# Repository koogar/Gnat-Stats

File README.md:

Gnat-Stats is an open-source project that transforms a small OLED display into a real-time PC hardware performance monitor using Arduino-compatible microcontrollers. It visually presents metrics like CPU and GPU temperatures, loads, and system memory usage.([GitHub][1], [GitHub][2])

---

## 🔧 Features

* **Real-Time Monitoring**: Displays CPU/GPU temperatures, loads, and system RAM usage.
* **Compact Design**: Utilizes SSD1306 or SH1106 OLED displays for a minimal footprint.
* **Customizable Layouts**: Offers multiple display styles and anti-burn features.
* **Hardware Compatibility**: Supports boards like Seeeduino XIAO, Adafruit QT Py, and ESP32.
* **Serial Communication**: Receives data from a Windows client via USB serial.([GitHub][3])

---

## 🛠️ Getting Started

1. **Hardware Setup**:

   * Connect an SSD1306 or SH1106 OLED display to your microcontroller.
   * Ensure proper I2C connections and address configuration.([GitHub][3])
   * For detailed setup guides and tutorials, refer to the [Gnat-Stats OLED Display Hook-Up Guide](https://runawaybrainz.blogspot.com/2021/03/phat-stats-ssd1306-oled-hook-up-guide.html).

2. **Software Installation**:

   * Install necessary Arduino libraries:

     * Adafruit NeoPixel
     * Adafruit SSD1306
     * Adafruit SH110X
     * Adafruit GFX
     * Adafruit BusIO
   * Configure your board using the appropriate Board Manager URLs:

     * For Seeeduino XIAO:

       ```
       https://files.seeedstudio.com/arduino/package_seeeduino_boards_index.json
       ```

3. **Firmware Upload**:

   * Open the desired `.ino` file (e.g., `GnatStats_V1.7.Base.ino`) in the Arduino IDE.
   * Select the correct board and port.
   * Upload the sketch to your microcontroller.([GitHub][3])

4. **Windows Client**:

   * Install the [HardwareSerialMonitor](https://github.com/koogar/HardwareSerialMonitor) on your Windows PC to relay performance data.
3. **Configuration**:

   * Adjust settings within the Gnat-Stats firmware and HardwareSerialMonitor to match your hardware setup and monitoring preferences.

---

## 📜 License

This project is licensed under the [GPL-2.0 License](https://github.com/koogar/Gnat-Stats/blob/master/LICENSE.txt).

Gnat-Stats, Phat-Stats, Tacho-Stats, uVolume & HardwareSerialMonitor 
Copyright (C) 2016  Colin Conway, Rupert Hirst and contributors
 
This program is free software; you can redistribute it and/or
modify it under the terms of the GNU General Public License
as published by the Free Software Foundation; either version 2
of the License, or (at your option) any later version.

This program is distributed in the hope that it will be useful,
but WITHOUT ANY WARRANTY; without even the implied warranty of
MERCHANTABILITY or FITNESS FOR A PARTICULAR PURPOSE.  See the
GNU General Public License for more details.

You should have received a copy of the GNU General Public License
along with this program; If not, see <http://www.gnu.org/licenses/>.

---

For more details, visit the [Gnat-Stats GitHub Repository](https://github.com/koogar/Gnat-Stats).

[1]: https://github.com/koogar/Gnat-Stats/releases?utm_source=chatgpt.com "Releases · koogar/Gnat-Stats - GitHub"
[2]: https://github.com/koogar/Gnat-Stats/blob/master/GnatStats_V1.7.Base/DisplayStats.ino?utm_source=chatgpt.com "Gnat-Stats/GnatStats_V1.7.Base/DisplayStats.ino at master - GitHub"
[3]: https://github.com/koogar/Gnat-Stats/blob/master/GnatStats_V1.7.Base/GnatStats_V1.7.Base.ino?utm_source=chatgpt.com "Gnat-Stats/GnatStats_V1.7.Base/GnatStats_V1.7.Base.ino at ... - GitHub"
[4]: https://github.com/koogar/Gnat-Stats?utm_source=chatgpt.com "GitHub - koogar/Gnat-Stats: GnatStats Tiny OLED Arduino PC Hardware ..."

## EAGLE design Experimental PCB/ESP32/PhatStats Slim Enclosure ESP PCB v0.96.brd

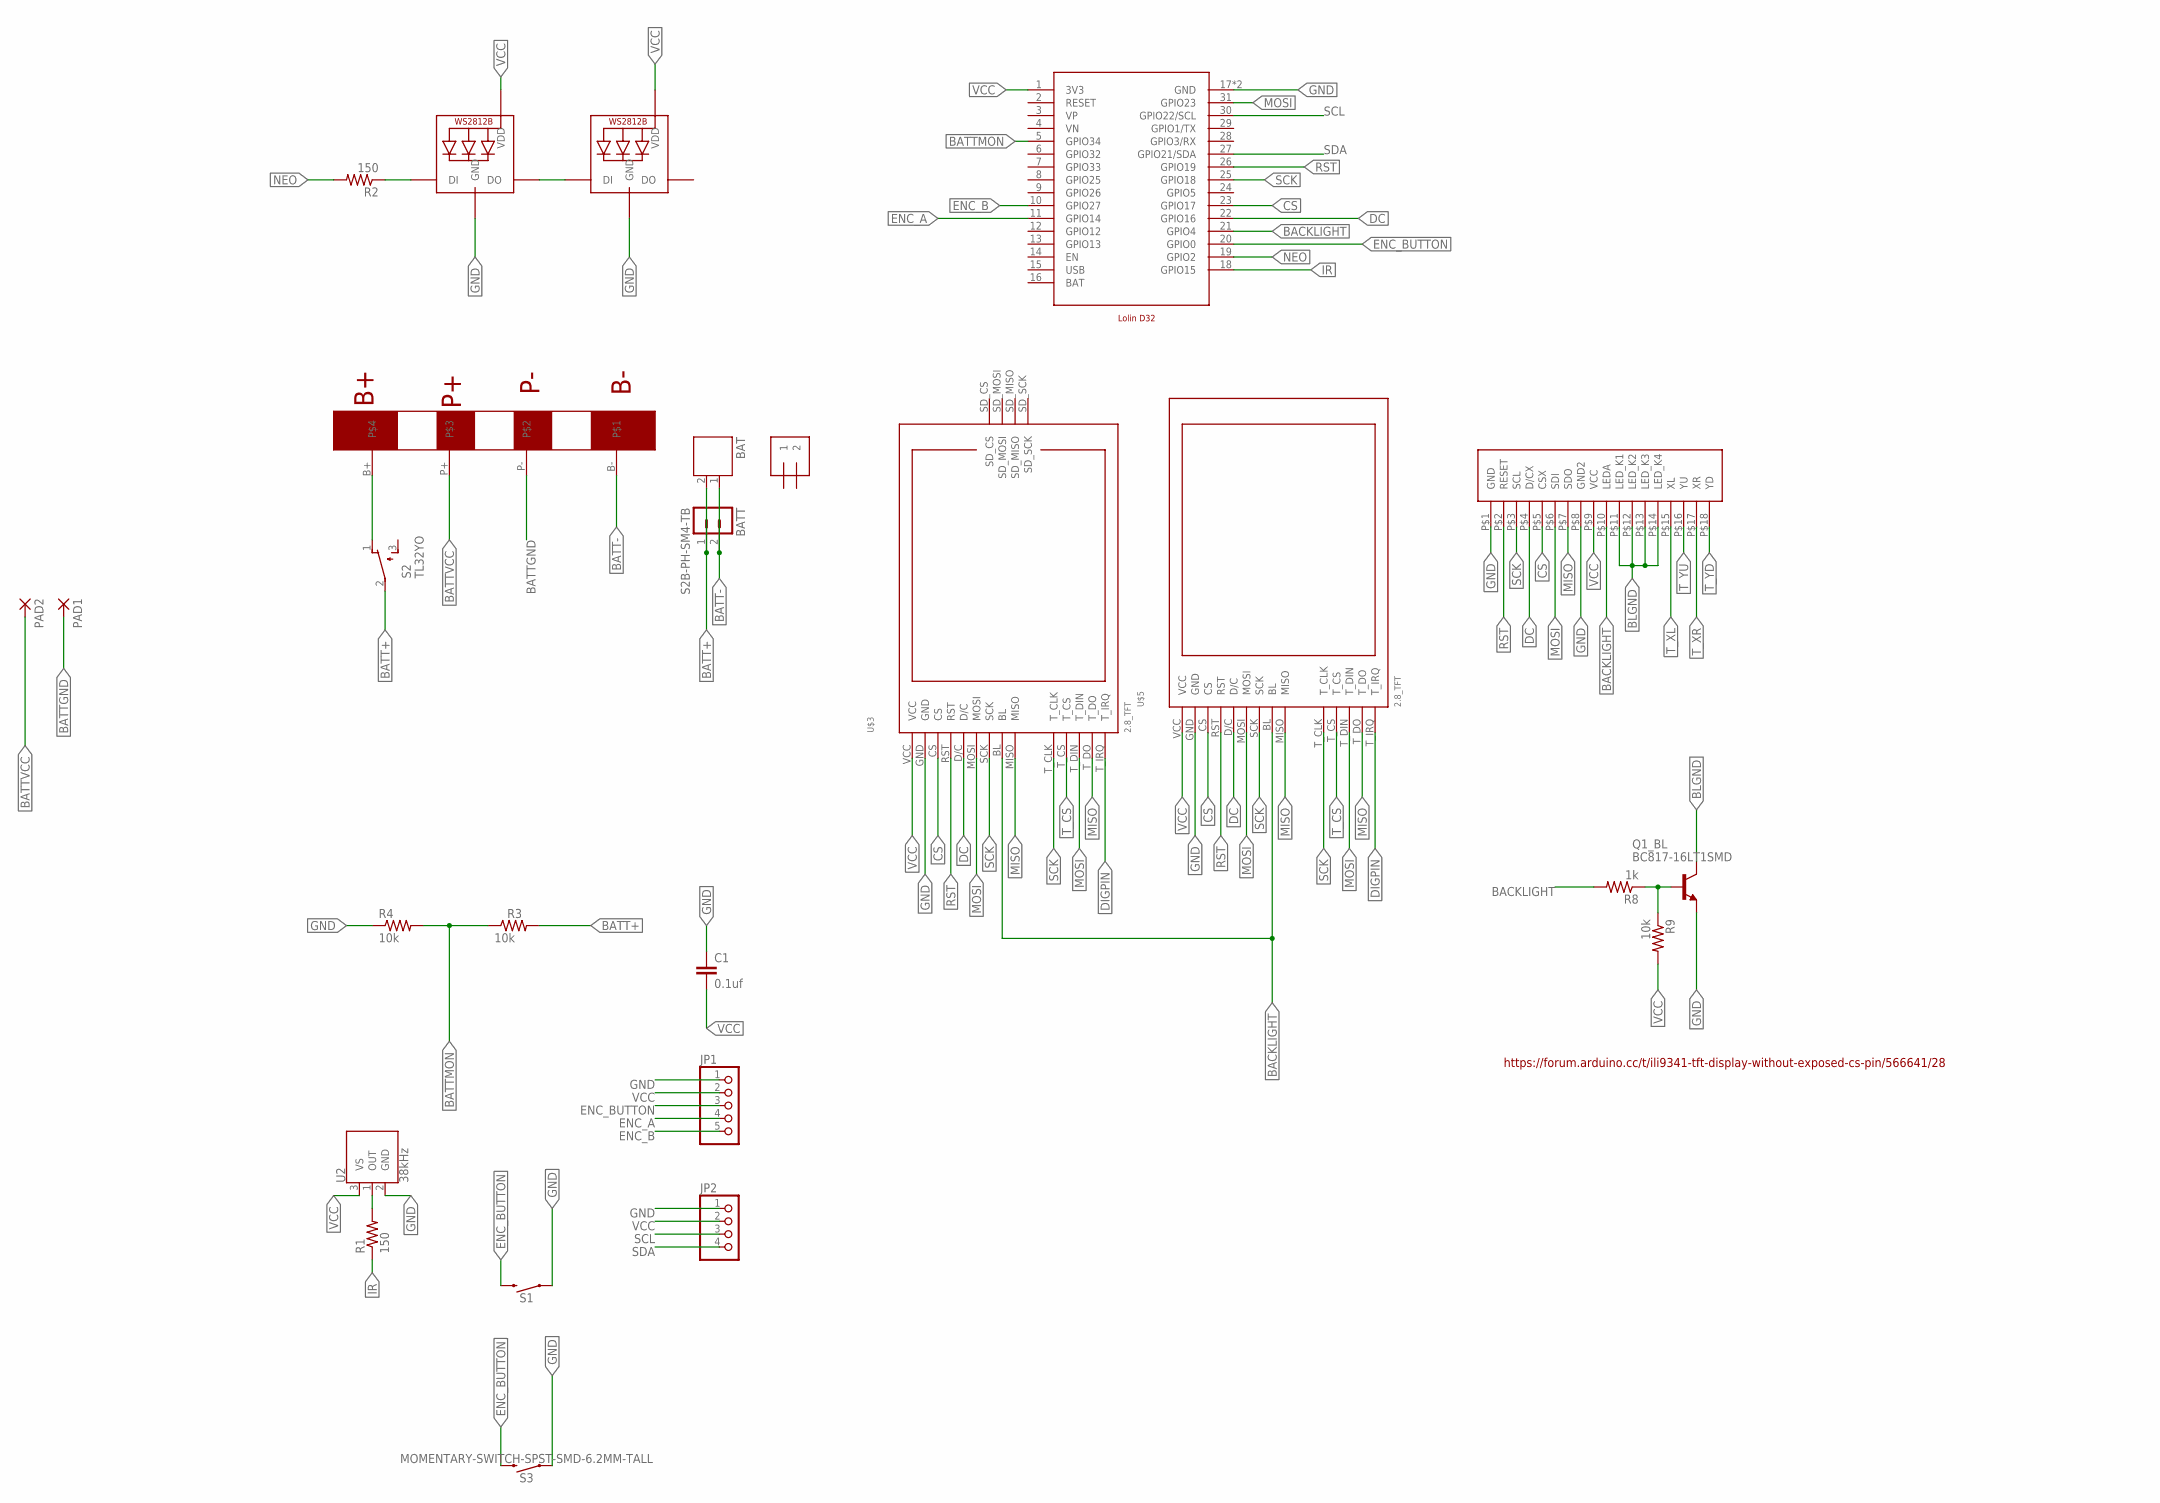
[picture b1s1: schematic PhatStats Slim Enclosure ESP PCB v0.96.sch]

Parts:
0: ILI9341-2.8
BAT: JST-PH2
BATT: S2B-PH-SM4-TB
BMS: DW01BATTERYPROT
C1: 0.1uf; C1206
J1: 1X2-3.5MM
JP1: PINHD-1X5; 1X05
JP2: PINHD-1X4; 1X04
NEO1, NEO2: WS2812B5050; WS2812B
PAD1, PAD2: WIREPADSMD5-1,8; 5-1,8
Q1_BL: BC817-16LT1SMD; SOT23-BEC
R1, R2: 150; M1206
R3, R4, R9: 10k; M1206
R8: 1k; M1206
S1: MOMENTARY-SWITCH-SPST-PTH-6.0MM; TACTILE_SWITCH_PTH_6.0MM
S2: TL32YO; TL3XYO
S3: MOMENTARY-SWITCH-SPST-SMD-6.2MM-TALL; TACTILE_SWITCH_SMD_6.2MM_TALL
U2: 38kHz; TSOP382
U$2: LOLIND32
U$3, U$5: 2.8_TFT

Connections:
BACKLIGHT: 0.P$10 (LEDA), R8.2, U$2.21 (GPIO4), U$3.BL, U$5.BL
BAT: U$2.16 (BAT)
BATT+: BAT.2, BATT.1, R3.2, S2.2
BATT-: BAT.1, BATT.2, BMS.B-
BATTGND: BMS.P-, PAD1.1
BATTMON: R3.1, R4.2, U$2.5 (GPIO34)
BATTVCC: BMS.P+, PAD2.1
BLGND: 0.P$11 (LED_K1), 0.P$12 (LED_K2), 0.P$13 (LED_K3), 0.P$14 (LED_K4), Q1_BL.C
CS: 0.P$5 (CSX), U$2.23 (GPIO17), U$3.CS, U$5.CS
DC: 0.P$4 (D/CX), U$2.22 (GPIO16), U$3.D/C, U$5.D/C
DIGPIN: U$3.T_IRQ, U$5.T_IRQ
ENC_A: JP1.4, U$2.11 (GPIO14)
ENC_B: JP1.5, U$2.10 (GPIO27)
ENC_BUTTON: JP1.3, S1.3 (2), S3.B2 (2), U$2.20 (GPIO0)
GND: 0.P$1 (GND), 0.P$8 (GND2), C1.1, JP1.1, JP2.1, NEO1.3-GND (GND), NEO2.3-GND (GND), Q1_BL.E, R4.1, S1.1, S3.A2 (1), U2.2 (GND), U$2.17 (GND), U$2.32 (GND), U$3.GND, U$5.GND
IR: R1.1, U$2.18 (GPIO15)
MISO: 0.P$7 (SDO), U$3.MISO, U$3.T_DO, U$5.MISO, U$5.T_DO
MOSI: 0.P$6 (SDI), U$2.31 (GPIO23), U$3.MOSI, U$3.T_DIN, U$5.MOSI, U$5.T_DIN
unnamed: BMS.B+, S2.1 (O)
unnamed: NEO1.2-DOUT (DO), NEO2.4-DIN (DI)
unnamed: R1.2, U2.1 (OUT)
unnamed: NEO1.4-DIN (DI), R2.1
unnamed: Q1_BL.B, R8.1, R9.1
NEO: R2.2, U$2.19 (GPIO2)
RST: 0.P$2 (RESET), U$2.26 (GPIO19), U$3.RST, U$5.RST
SCK: 0.P$3 (SCL), U$2.25 (GPIO18), U$3.SCK, U$3.T_CLK, U$5.SCK, U$5.T_CLK
SCL: JP2.3, U$2.30 (GPIO22/SCL)
SDA: JP2.4, U$2.27 (GPIO21/SDA)
T_CS: U$3.T_CS, U$5.T_CS
T_XL: 0.P$15 (XL)
T_XR: 0.P$17 (XR)
T_YD: 0.P$18 (YD)
T_YU: 0.P$16 (YU)
USB: U$2.15 (USB)
VCC: 0.P$9 (VCC), C1.2, JP1.2, JP2.2, NEO1.1-VDD (VDD), NEO2.1-VDD (VDD), R9.2, U2.3 (VS), U$2.1 (3V3), U$3.VCC, U$5.VCC

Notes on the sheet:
https://forum.arduino.cc/t/ili9341-tft-display-without-exposed-cs-pin/566641/28

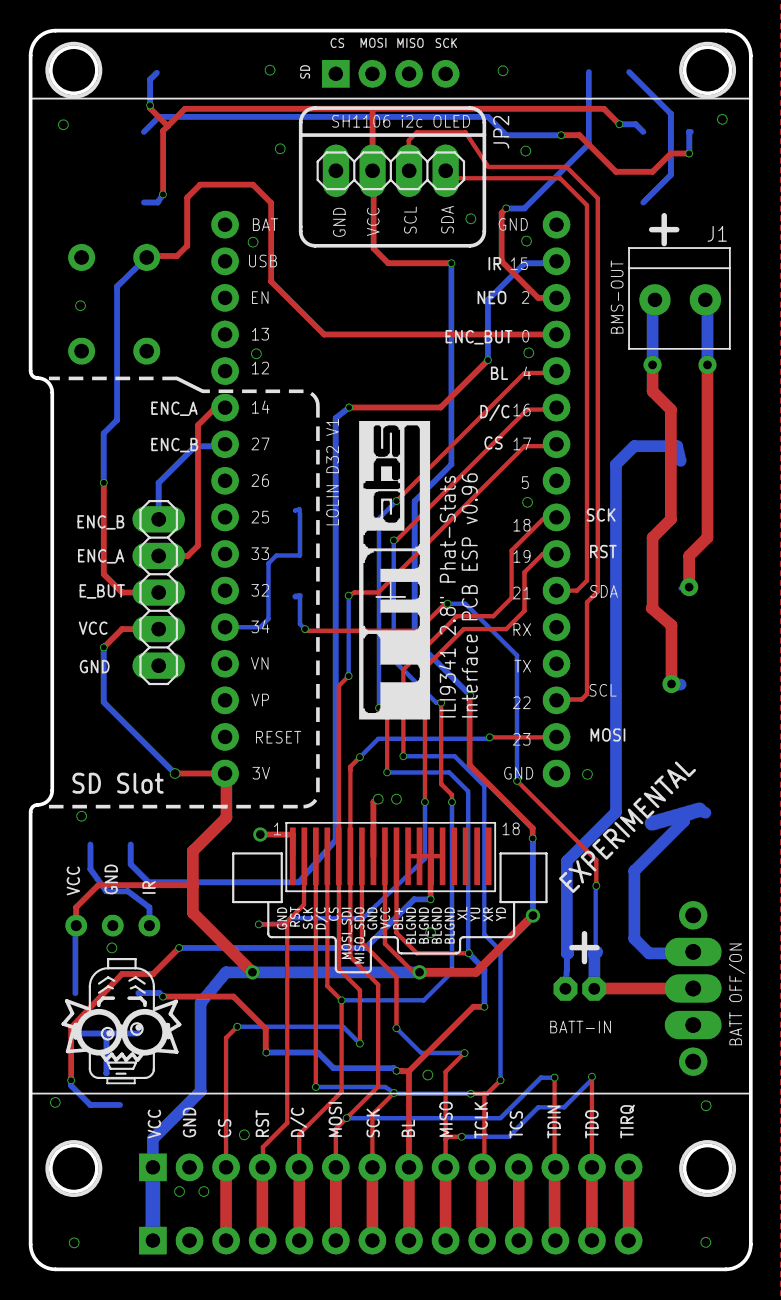
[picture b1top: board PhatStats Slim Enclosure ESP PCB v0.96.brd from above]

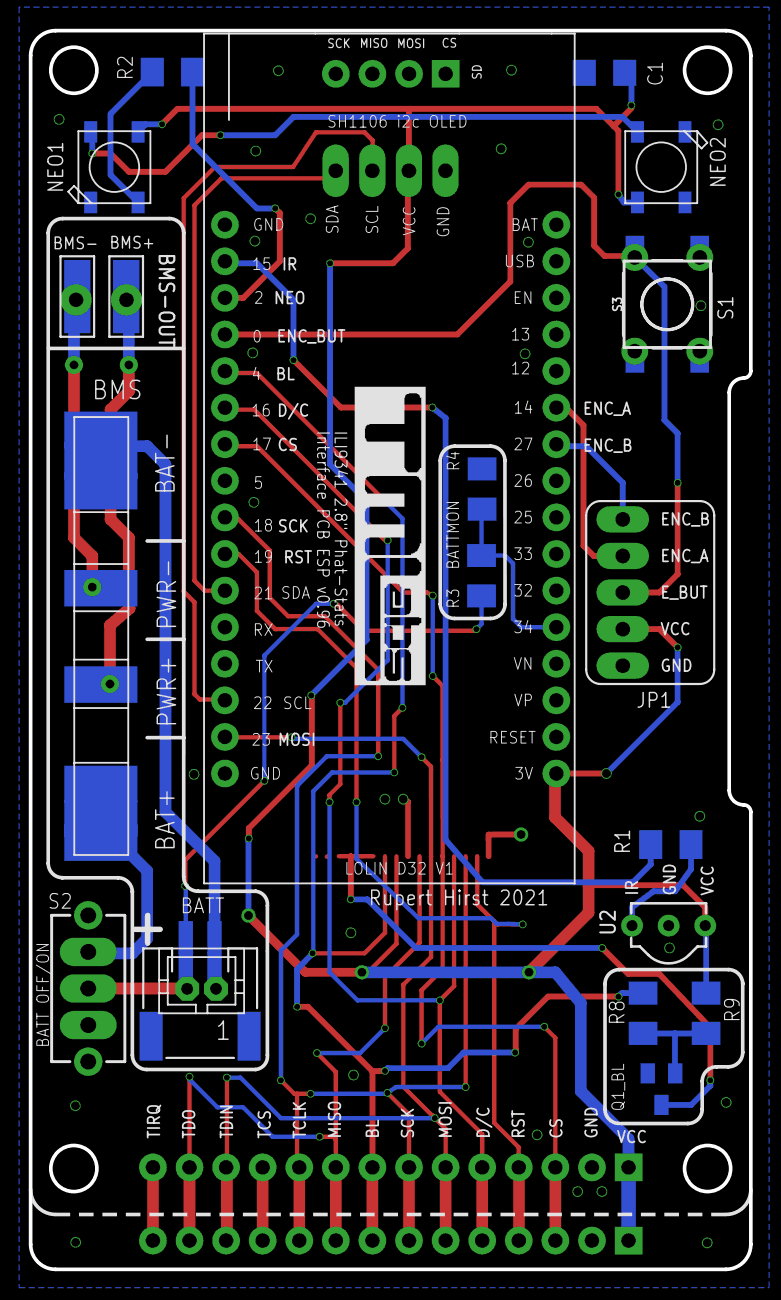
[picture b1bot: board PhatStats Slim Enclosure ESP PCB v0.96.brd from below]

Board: 2 copper layers, 50.0 x 86.0 mm, 29 parts (21 on the bottom side), 29 nets.

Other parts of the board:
U$6: MADPROF
U$9, U$10: TMSLOGO_INVERTED

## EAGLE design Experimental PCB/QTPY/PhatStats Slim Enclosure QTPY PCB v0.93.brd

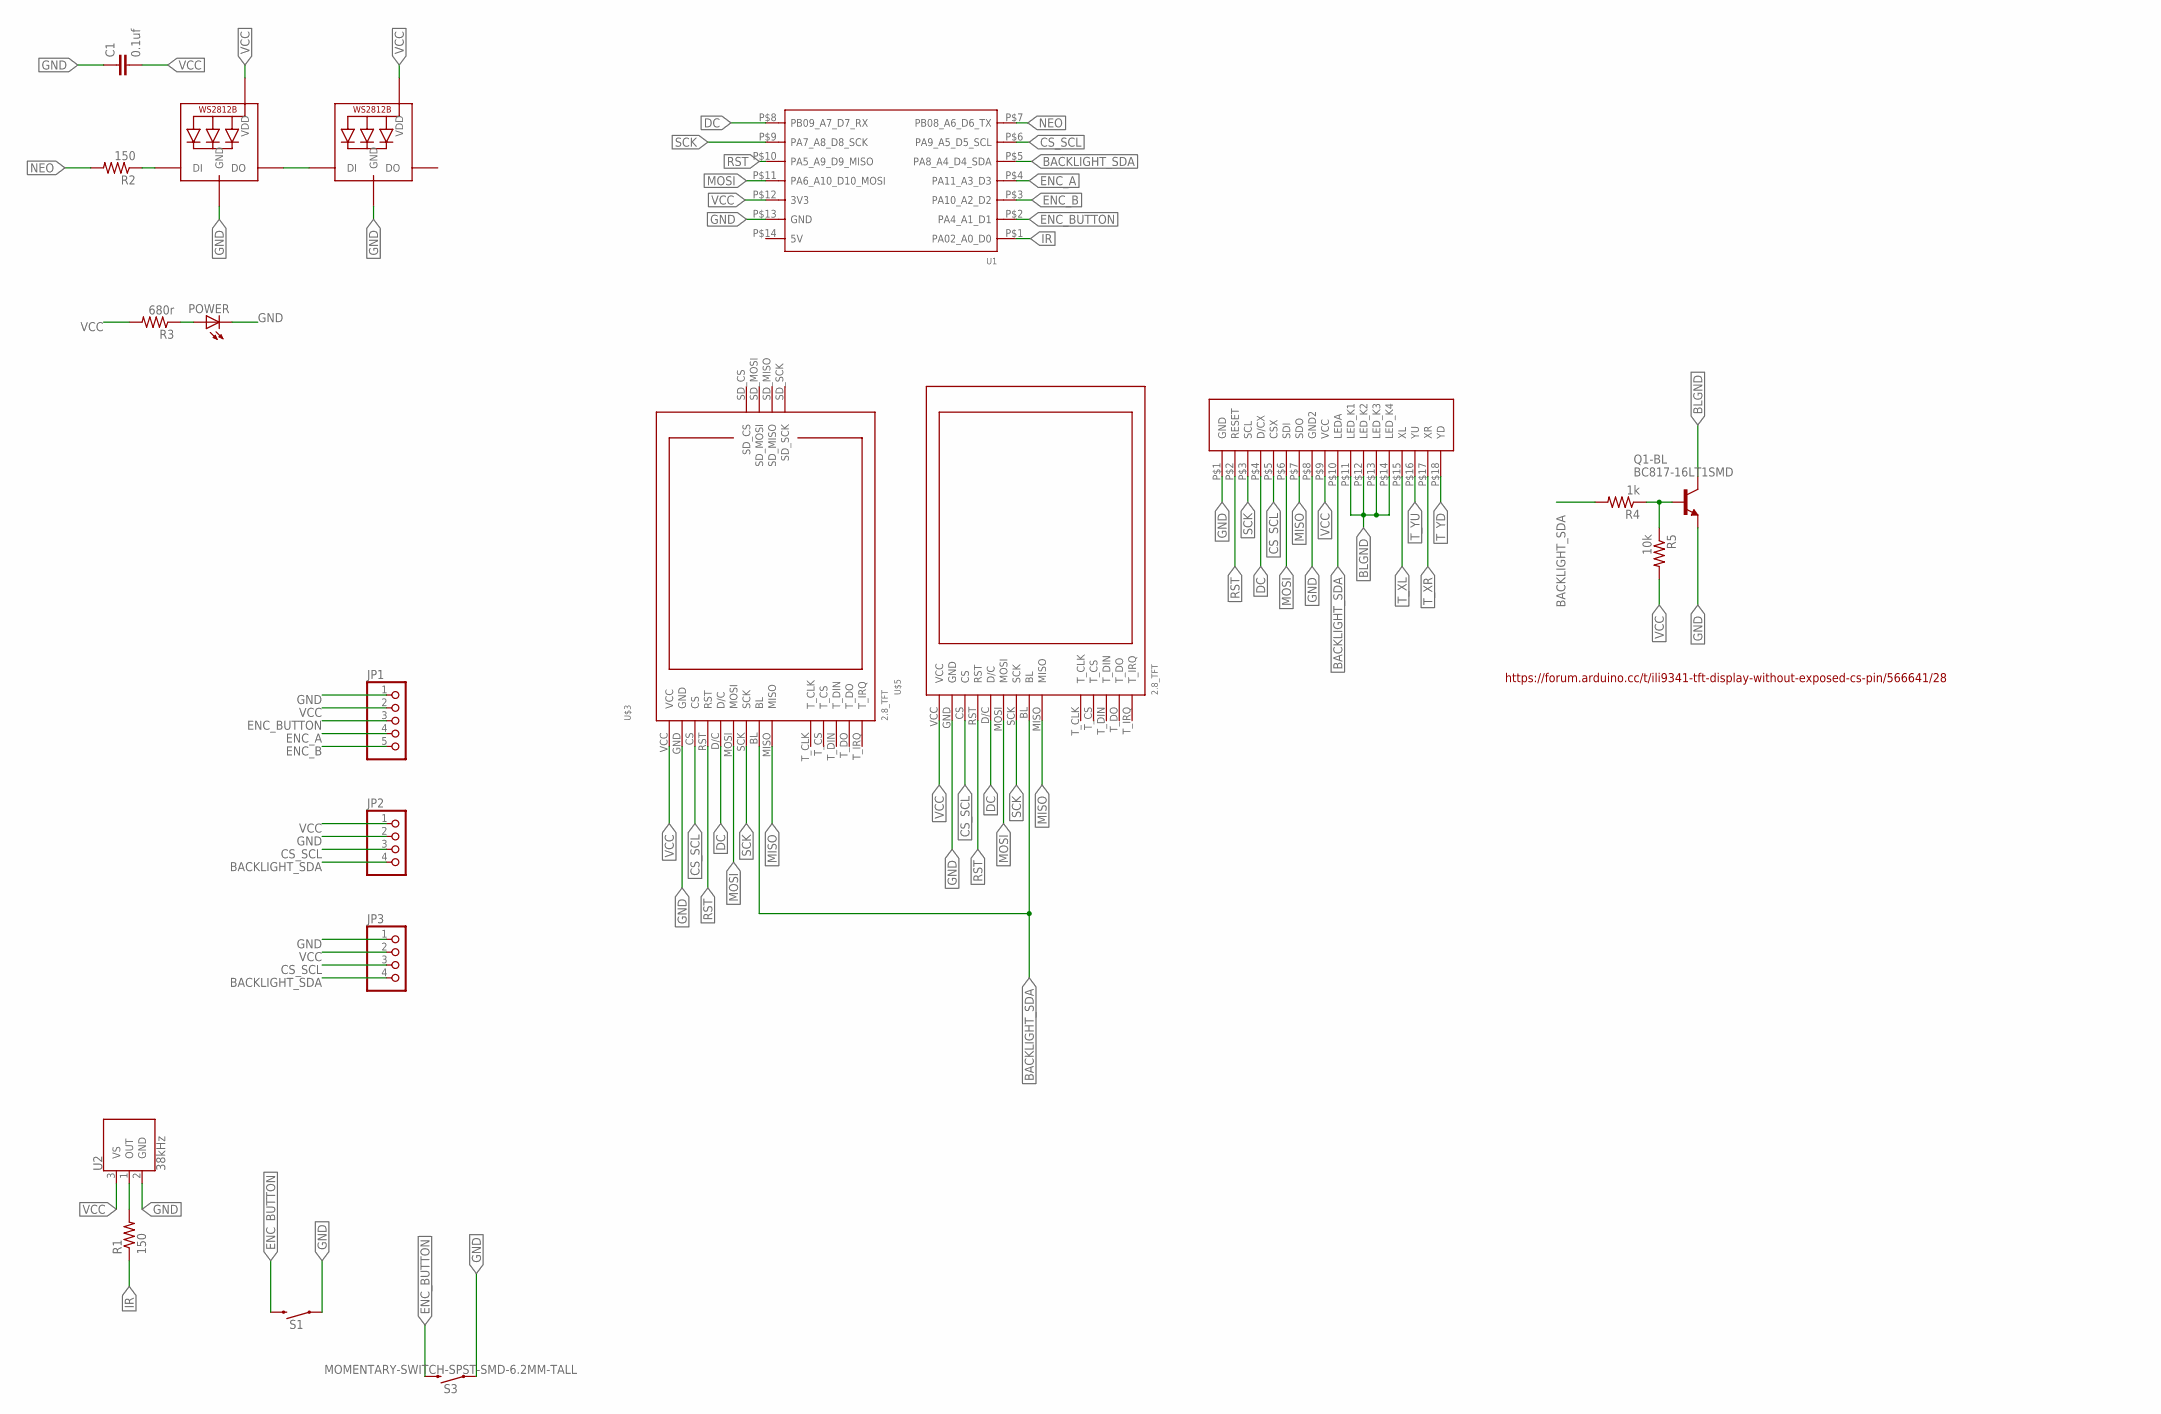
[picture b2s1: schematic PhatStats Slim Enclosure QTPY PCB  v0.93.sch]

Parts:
0: ILI9341-2.8
C1: 0.1uf; C1206
JP1: PINHD-1X5; 1X05
JP2, JP3: PINHD-1X4; 1X04
NEO1, NEO2: WS2812B5050; WS2812B
POWER: LEDCHIPLED_1206; CHIPLED_1206
Q1-BL: BC817-16LT1SMD; SOT23-BEC
R1, R2: 150; M1206
R3: 680r; M1206
R4: 1k; M1206
R5: 10k; M1206
S1: MOMENTARY-SWITCH-SPST-PTH-6.0MM; TACTILE_SWITCH_PTH_6.0MM
S3: MOMENTARY-SWITCH-SPST-SMD-6.2MM-TALL; TACTILE_SWITCH_SMD_6.2MM_TALL
U1: MOUDLE-SEEEDUINO-XIAO; MOUDLE14P-2.54-21X17.8MM
U2: 38kHz; TSOP382
U$3, U$5: 2.8_TFT

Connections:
BACKLIGHT_SDA: 0.P$10 (LEDA), JP2.4, JP3.4, R4.2, U1.P$5 (PA8_A4_D4_SDA), U$3.BL, U$5.BL
BLGND: 0.P$11 (LED_K1), 0.P$12 (LED_K2), 0.P$13 (LED_K3), 0.P$14 (LED_K4), Q1-BL.C
CS_SCL: 0.P$5 (CSX), JP2.3, JP3.3, U1.P$6 (PA9_A5_D5_SCL), U$3.CS, U$5.CS
DC: 0.P$4 (D/CX), U1.P$8 (PB09_A7_D7_RX), U$3.D/C, U$5.D/C
ENC_A: JP1.4, U1.P$4 (PA11_A3_D3)
ENC_B: JP1.5, U1.P$3 (PA10_A2_D2)
ENC_BUTTON: JP1.3, S1.3 (2), S3.B2 (2), U1.P$2 (PA4_A1_D1)
GND: 0.P$1 (GND), 0.P$8 (GND2), C1.1, JP1.1, JP2.2, JP3.1, NEO1.3-GND (GND), NEO2.3-GND (GND), POWER.C, Q1-BL.E, S1.1, S3.A2 (1), U1.P$13 (GND), U2.2 (GND), U$3.GND, U$5.GND
IR: R1.1, U1.P$1 (PA02_A0_D0)
MISO: 0.P$7 (SDO), U$3.MISO, U$5.MISO
MOSI: 0.P$6 (SDI), U1.P$11 (PA6_A10_D10_MOSI), U$3.MOSI, U$5.MOSI
unnamed: POWER.A, R3.1
unnamed: Q1-BL.B, R4.1, R5.1
unnamed: R1.2, U2.1 (OUT)
unnamed: NEO1.4-DIN (DI), R2.1
NEO: R2.2, U1.P$7 (PB08_A6_D6_TX)
NEODATA: NEO1.2-DOUT (DO), NEO2.4-DIN (DI)
RST: 0.P$2 (RESET), U1.P$10 (PA5_A9_D9_MISO), U$3.RST, U$5.RST
SCK: 0.P$3 (SCL), U1.P$9 (PA7_A8_D8_SCK), U$3.SCK, U$5.SCK
T_XL: 0.P$15 (XL)
T_XR: 0.P$17 (XR)
T_YD: 0.P$18 (YD)
T_YU: 0.P$16 (YU)
VCC: 0.P$9 (VCC), C1.2, JP1.2, JP2.1, JP3.2, NEO1.1-VDD (VDD), NEO2.1-VDD (VDD), R3.2, R5.2, U1.P$12 (3V3), U2.3 (VS), U$3.VCC, U$5.VCC

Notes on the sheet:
https://forum.arduino.cc/t/ili9341-tft-display-without-exposed-cs-pin/566641/28

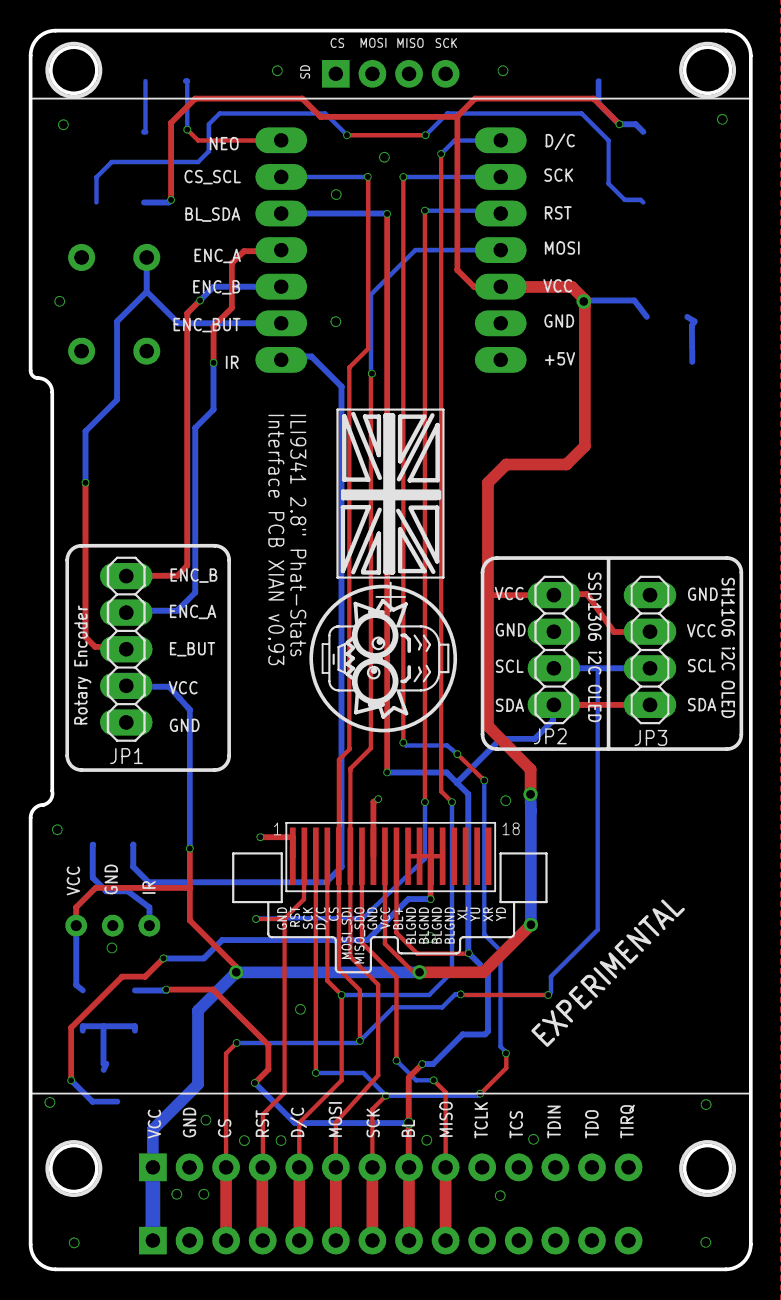
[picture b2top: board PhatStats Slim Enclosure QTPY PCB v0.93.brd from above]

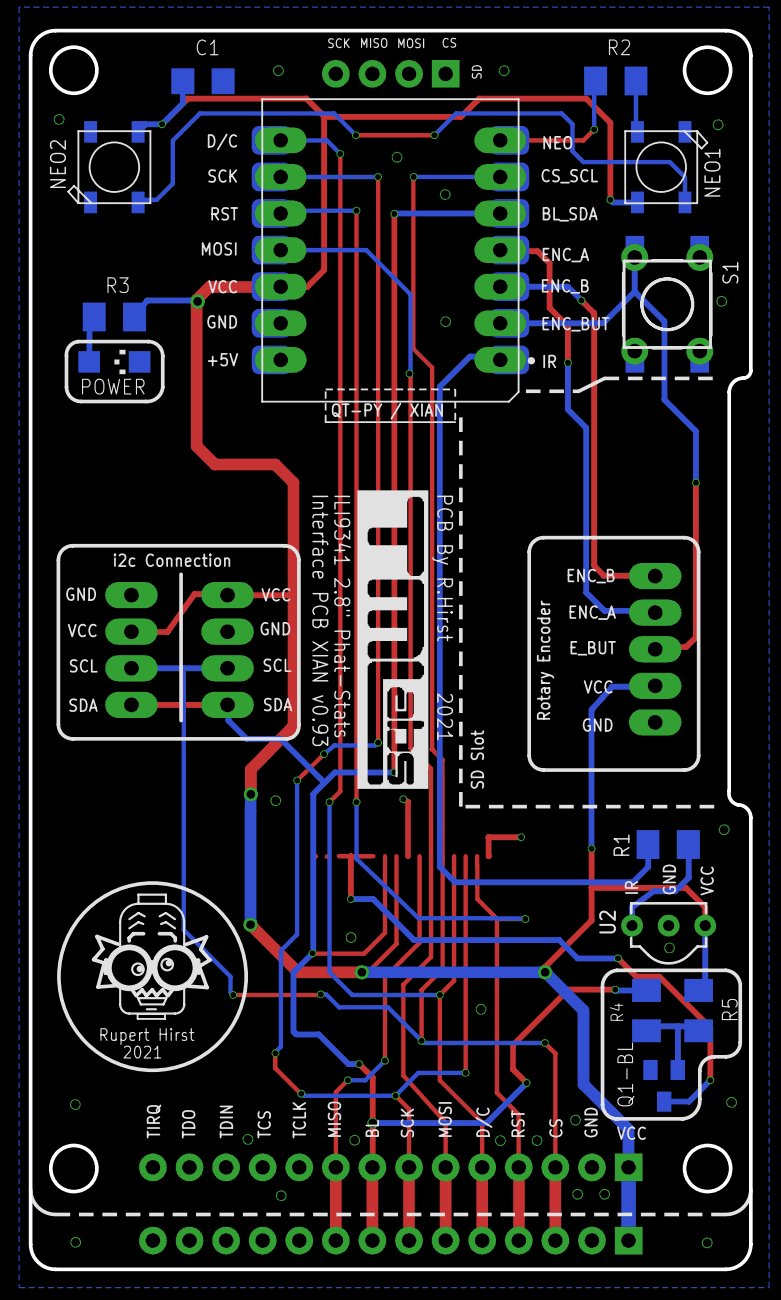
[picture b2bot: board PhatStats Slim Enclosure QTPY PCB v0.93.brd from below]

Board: 2 copper layers, 50.0 x 86.0 mm, 23 parts (16 on the bottom side), 20 nets.

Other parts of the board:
U$1: TMSLOGO_PROF_UNION_LRG
U$6: MADPROF
U$9: TMSLOGO_INVERTED

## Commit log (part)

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2020-06-06 GnatStats_ProMicro_STM32_TFT_V1.5
2020-06-06 Gnat Stats
    TallmanLabs
    Gnat Stats Arduino PC Performance Display
2021-01-13 GnatStats
2021-01-13 Gnat Stats Arduino Serial Display
2021-01-13 GnatStats Old Versions
2021-01-13 GnatStats Arduino PC Performance Serial Display
2021-01-13 Phat Stats Arduino PC Performance Serial Display
2021-01-13 Readme
2021-01-14 Gnat-Tacho Overlay 47.75mm
2021-01-14 Images
2021-01-15 Neopixel Pin name change to NEOPIN
2021-01-18 digitalWrite Backlight LOW to stop PWM idle flicker on ATSAMD
2021-01-28 1.6.2 update
2021-01-29 GPU Memory Update Tweak
2021-01-29 Tweak
2021-02-06 Add uVolume
2021-02-06 µVolume
2021-02-07 Multi MCU TFT
2021-02-09 Multi MCU
2021-02-09 Pin Out TXT
2021-02-10 Add Adafruit QT-PY TFT PhatStats
2021-02-10 clean up
2021-02-12 cleanup
2021-02-18 change RX circle size
2021-02-22 Change Button Pin from 7 to 5
2021-02-25 Landscape Tweaks
2021-02-27 Shorten Overclock Frequency % Sum
2021-03-06 Depreciated
2021-03-06 Create Screen Images Folder
2021-03-10 Pin change on rotary encoder and button
2021-03-10 Old Versions
2021-03-12 licence
2021-03-12 Licence info
2021-03-12 Adafruit QT-PY Release
2021-03-12 BluePill Version
2021-03-12 Experimental
2021-03-12 pin update
2021-03-12 old Version
2021-03-13 Add Seeeduino XIAO support
2021-03-13 add URL
2021-03-13 Add URL to Pin Ref
2021-03-15 Display Char Spacing
2021-03-15 LibreNet Version Experimental
2021-03-28 Freq Trailing Char Fix
2021-03-30 ESP32 OLED
2021-03-31 Add XIAO Board URLs
2021-03-31 licence and pins.txt
2021-04-01 Clean up info
2021-04-01 update info
2021-04-03 NooB Check
2021-04-03 Update NooB test
2021-04-03 Hook Up Guide
2021-04-06 DEPRECIATE STM32
2021-04-06 delete
2021-04-06 Zip-a-Dee-Doo-Dah
2021-04-06 Name Change
2021-04-07 Alternate Pin Layout
2021-04-08 Pin Changes and InfraRed
2021-04-08 Optimise Pins
2021-04-08 Moved
2021-04-10 Add Adafruit Driver Link
2021-04-10 Move to IR folder
2021-04-15 Clean folders up
2021-04-21 Last STM32 BluePill update
2021-04-21 STM32 Support Warning
2021-04-24 Change Frequency Gains MHZ to smaller font
2021-04-24 update Frequency Gain MHz font size
2021-05-04 enableTX_LED
2021-05-17 update Circle Gauge
2021-06-24 Battery Monitor Update
2021-06-28 CPU/GPU name updates
2021-07-22 make images folder
2021-07-22 include images
2021-09-05 ATSAMD SH1106
2021-09-09 Update QTPY IR
2021-09-09 arrange types
2021-09-10 Add dimming on SH1106
2021-09-10 Add Display Dim
2021-09-12 SPI Support
2021-09-12 spi update
2021-09-12 add SH1106 Dimming
2021-09-12 resize
2025-04-05 add robot eyes on standby

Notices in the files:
parts and their libraries:
SparkFun-Switches: Licensing: Creative Commons ShareAlike 4.0 International - https://creativecommons.org/licenses/by-sa/4.0
